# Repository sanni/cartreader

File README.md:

<br>    
<br>    
<br>   
<br>
We have moved, please visit us at https://github.com/oscartreader 🚀
<br>    
<br>    
<br>   
<br>
<br>    
<br>    
<br>   

# Open Source Cartridge Reader
This project represents a community-driven effort to provide an easy to build and easy to modify cartridge dumper.
Its main purpose is to dump a video game's ROM and save file to an SD card without the need of a PC.

For any questions you can use the [Discussions](https://github.com/sanni/cartreader/discussions) and/or [Issues](https://github.com/sanni/cartreader/issues) section here on GitHub, visit the accompanying thread in the [Arduino Forum](http://forum.arduino.cc/index.php?topic=158974.9001) or check out our [community discord server](https://discord.gg/YVxv7BnzXt), where you can reach most of the devs directly.

Also be sure to check the guides in the [Wiki](https://github.com/sanni/cartreader/wiki) too.

Happy making. 🔧🔨😊

#### Features:
- Modular design
- Stand-alone operation
- Easy to modify open-source code
- Portable when used together with a power bank

#### Supported Systems:
- NES/Famicom/Family Basic
- Super Nintendo/Super Famicom (including SF Memory, Satellaview, Sufami Turbo, and Game Processor RAM Cassettes)
- Nintendo 64 (including Controller Pak, Gameshark, and Xplorer 64)
- Game Boy Color (including GB Memory, Codebreaker, and Gameshark)
- Game Boy Advance
- Sega Mega Drive/Genesis
- Sega Master System

#### Supported with adapters:
- Virtual Boy
- Pokémon Mini
- Sega Game Gear
- Sega Mark III
- Sega SG-1000/SC-3000
- Sega Cards
- PC Engine/TurboGrafx-16/SuperGrafx
- WonderSwan (Color)
- NeoGeo Pocket (Color)
- Intellivision
- ColecoVision
- Benesse Pocket Challenge W
- Benesse Pocket Challenge V2
- Watara Supervision
- Atari 8-bit Computer (400/800/XL/XE)
- Atari 2600/5200/7800
- Atari Lynx
- Atari Jaguar
- Emerson Arcadia 2001
- Fairchild Channel F
- Magnavox Odyssey 2/Philips Videopac+
- Super A'Can
- MSX
- Casio PV-1000
- Casio Loopy
- Commodore VIC-20
- Commodore 64
- Vectrex
- Bally Astrocade
- Bandai Little Jammer
- Bandai Little Jammer Pro
- LeapFrog Leapster (L-MAX/Leapster2)
- RCA Studio II
- Texas Instruments TI-99
- Tomy Pyuuta
- TRS-80 Color Computer
- Vtech V.Smile (Baby/V.Motion)
- CPS3

#### Open Source Licenses:
- Software(everything in Cart_Reader folder) = GPL v3
- Hardware(everything in hardware folder) = CC BY 4.0
- Documentation(everything in the Wiki) = CC0 1.0

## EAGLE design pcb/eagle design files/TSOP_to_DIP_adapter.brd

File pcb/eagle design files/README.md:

With these Eagle files you can easily make your own PCB variants.    
For best compatibility be sure to use the win32 version of Eagle 7.6.0 downloaded from [here](http://eagle.autodesk.com/eagle/software-versions/2).    
All PCBs were autorouted with FreeRouting for which you need the [Java 8 RE](https://www.java.com/de/download/manual.jsp).    

#### Quick tutorial on modifying an adapter PCB:     
- Install Eagle 7.6.0 Win32    
- Copy the cam, dru, lbr and ulp folders to the Eagle main dir.    
- Open the XXX_adapter.brd file that you want to modify in Eagle PCBs.    
- In the textfield type ripup; and execute by pressing Enter key twice.    
- Go to Schematic and Board view and do your changes, watch basic Eagle tutorials to learn how.    
- Once everything is done. Go back to Board view, then File ->  Run ULP -> eagle2freerouterV6-6.ulp -> Create DSN file.     
- In Windows Explorer execute FreeRouting1.jar in ulp dir and open the XXX_adapter.dsn file you created in the previous step.     
- Let it autoroute for some hours, once finished choose Export Eagle Session script.     
- Back in Eagle in the Board view go File -> Execute Script and select the XXX_adapter.scr you just exported.     
- Next go File -> Cam Processor, File -> Open -> Job and select Elecrow_Gerber_Generater_DrillAlign.cam, then Process Job to export the Gerber files.    
- Finally inspect your gerber files with [GerberLogix](https://www.easylogix.de/products_detail.php?prog_id=1) before uploading them to JLCPCB.

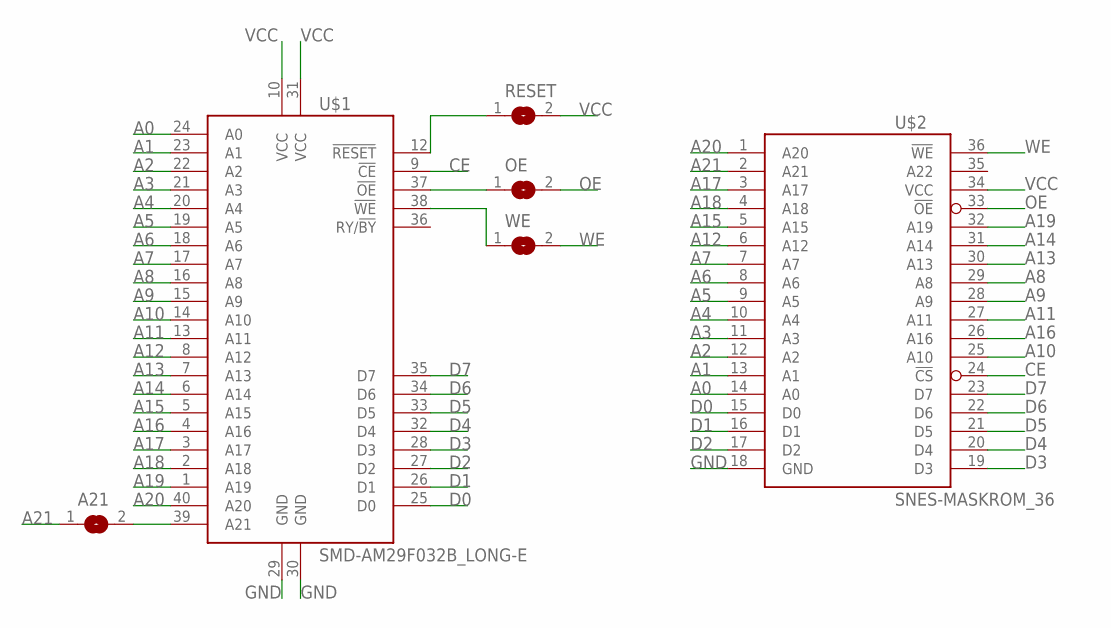
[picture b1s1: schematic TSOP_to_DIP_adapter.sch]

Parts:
A21: SMD-SOLDER_JUMPER_2; SJ
OE: SMD-SOLDER_JUMPER_2; SJ
RESET: SMD-SOLDER_JUMPER_2; SJ
U$1: SMD-AM29F032B_LONG-E; 40-TSOP_LONG
U$2: SNES-MASKROM_36; 36-PDIP
WE: SMD-SOLDER_JUMPER_2; SJ

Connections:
A0: U$1.24 (A0), U$2.14 (A0)
A1: U$1.23 (A1), U$2.13 (A1)
A2: U$1.22 (A2), U$2.12 (A2)
A3: U$1.21 (A3), U$2.11 (A3)
A4: U$1.20 (A4), U$2.10 (A4)
A5: U$1.19 (A5), U$2.9 (A5)
A6: U$1.18 (A6), U$2.8 (A6)
A7: U$1.17 (A7), U$2.7 (A7)
A8: U$1.16 (A8), U$2.29 (A8)
A9: U$1.15 (A9), U$2.28 (A9)
A10: U$1.14 (A10), U$2.25 (A10)
A11: U$1.13 (A11), U$2.27 (A11)
A12: U$1.8 (A12), U$2.6 (A12)
A13: U$1.7 (A13), U$2.30 (A13)
A14: U$1.6 (A14), U$2.31 (A14)
A15: U$1.5 (A15), U$2.5 (A15)
A16: U$1.4 (A16), U$2.26 (A16)
A17: U$1.3 (A17), U$2.3 (A17)
A18: U$1.2 (A18), U$2.4 (A18)
A19: U$1.1 (A19), U$2.32 (A19)
A20: U$1.40 (A20), U$2.1 (A20)
A21: A21.1, U$2.2 (A21)
CE: U$1.9 (!CE), U$2.24 (!CS)
D0: U$1.25 (D0), U$2.15 (D0)
D1: U$1.26 (D1), U$2.16 (D1)
D2: U$1.27 (D2), U$2.17 (D2)
D3: U$1.28 (D3), U$2.19 (D3)
D4: U$1.32 (D4), U$2.20 (D4)
D5: U$1.33 (D5), U$2.21 (D5)
D6: U$1.34 (D6), U$2.22 (D6)
D7: U$1.35 (D7), U$2.23 (D7)
GND: U$1.29 (GND), U$1.30 (GND), U$2.18 (GND)
unnamed: OE.1, U$1.37 (!OE)
unnamed: RESET.1, U$1.12 (!RESET)
unnamed: A21.2, U$1.39 (A21)
unnamed: U$1.38 (!WE), WE.1
OE: OE.2, U$2.33 (!OE)
VCC: RESET.2, U$1.10 (VCC), U$1.31 (VCC), U$2.34 (VCC)
WE: U$2.36 (!WE), WE.2

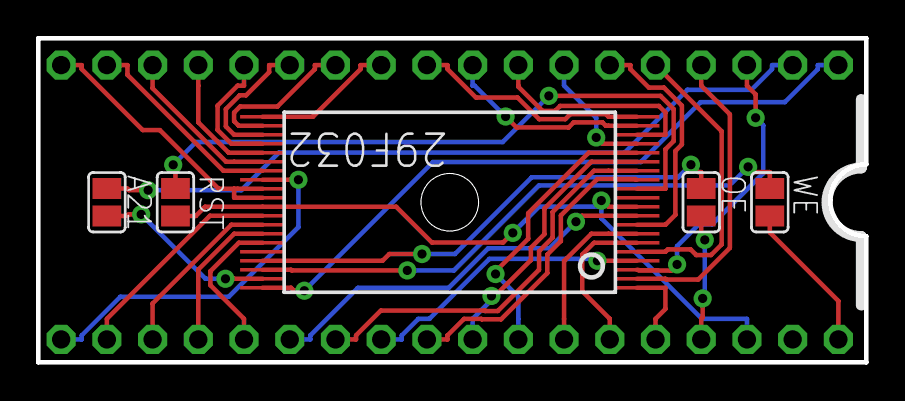
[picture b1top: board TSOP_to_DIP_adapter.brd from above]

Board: 2 copper layers, 46.0 x 18.0 mm, 6 parts (0 on the bottom side), 39 nets.

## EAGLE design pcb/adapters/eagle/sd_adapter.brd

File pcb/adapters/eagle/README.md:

With these Eagle files you can easily make your own PCB variants.    
For best compatibility be sure to use the win32 version of Eagle 7.6.0 downloaded from [here](http://eagle.autodesk.com/eagle/software-versions/2).    
All PCBs were autorouted with FreeRouting for which you need the [Java 8 RE](https://www.oracle.com/technetwork/java/javase/downloads/jre8-downloads-2133155.html).    

#### Quick tutorial on modifying an adapter PCB:     
- Install Eagle 7.6.0 Win32    
- Copy the cam, dru, lbr and ulp folders to the Eagle main dir.    
- Open the XXX_adapter.brd file that you want to modify in Eagle PCBs.    
- In the textfield type ripup; and execute by pressing Enter key twice.    
- Go to Schematic and Board view and do your changes, watch basic Eagle tutorials to learn how.    
- Once everything is done. Go back to Board view, then File ->  Run ULP -> eagle2freerouterV6-6.ulp -> Create DSN file.     
- In Windows Explorer execute FreeRouting1.jar in ulp dir and open the XXX_adapter.dsn file you created in the previous step.     
- Let it autoroute for some hours, once finished choose Export Eagle Session script.     
- Back in Eagle in the Board view go File -> Execute Script and select the XXX_adapter.scr you just exported.     
- Next go File -> Cam Processor, File -> Open -> Job and select Elecrow_Gerber_Generater_DrillAlign.cam, then Process Job to export the Gerber files.    
- Finally inspect your gerber files with [GerberLogix](https://www.easylogix.de/products_detail.php?prog_id=1) before uploading them to JLCPCB.

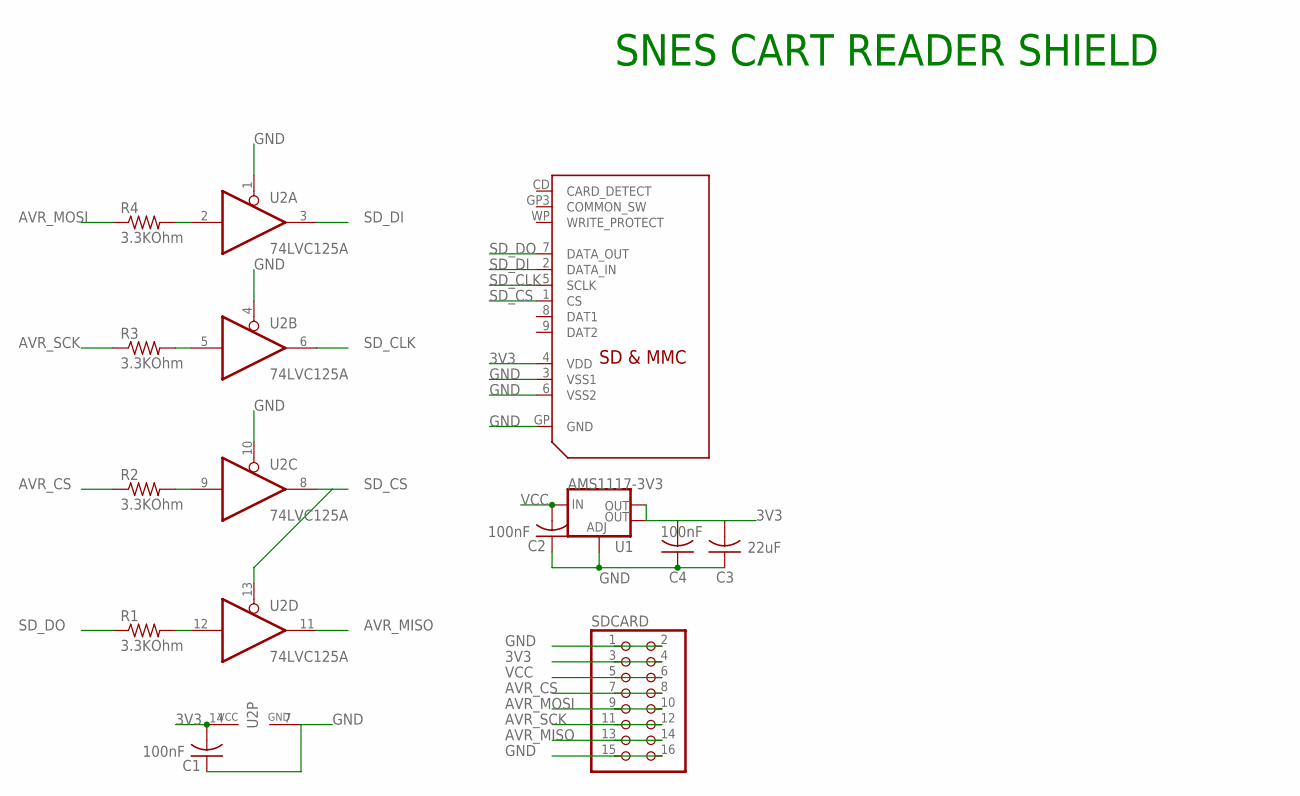
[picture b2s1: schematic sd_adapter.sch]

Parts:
C1, C2, C4: 100nF; C0805
C3: 22uF; C0805
R1, R2, R3, R4: 3.3KOhm; R0805
SDCARD: PINHD-2X8_2.54; 2X08
U1: AMS1117-3V3; SOT223
U2: 74LVC125A; TSSOP14
U$1: SDMMC06132; 06132

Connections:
3V3: C1.2, C3.2, C4.2, SDCARD.3, SDCARD.4, U1.2 (OUT), U1.4 (OUT), U2.14 (VCC), U$1.4 (VDD)
AVR_CS: R2.1, SDCARD.7, SDCARD.8
AVR_MISO: SDCARD.13, SDCARD.14, U2.11 (O)
AVR_MOSI: R4.1, SDCARD.9, SDCARD.10
AVR_SCK: R3.1, SDCARD.11, SDCARD.12
GND: C1.1, C2.1, C3.1, C4.1, SDCARD.1, SDCARD.2, SDCARD.15, SDCARD.16, U1.1 (ADJ), U2.1 (OE), U2.4 (OE), U2.7 (GND), U2.10 (OE), U$1.3 (VSS1), U$1.6 (VSS2), U$1.GP (GND)
unnamed: R1.2, U2.12 (I)
unnamed: R2.2, U2.9 (I)
unnamed: R3.2, U2.5 (I)
unnamed: R4.2, U2.2 (I)
SD_CLK: U2.6 (O), U$1.5 (SCLK)
SD_CS: U2.8 (O), U2.13 (OE), U$1.1 (CS)
SD_DI: U2.3 (O), U$1.2 (DATA_IN)
SD_DO: R1.1, U$1.7 (DATA_OUT)
VCC: C2.2, SDCARD.5, SDCARD.6, U1.3 (IN)

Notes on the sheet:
SNES CART READER SHIELD

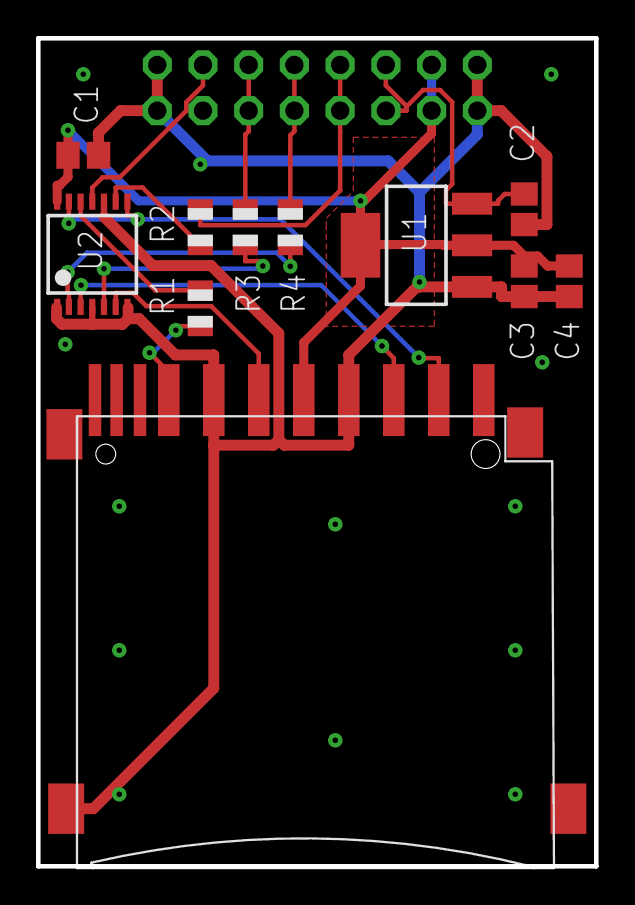
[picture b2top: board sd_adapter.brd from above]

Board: 2 copper layers, 31.0 x 46.0 mm, 12 parts (0 on the bottom side), 15 nets.

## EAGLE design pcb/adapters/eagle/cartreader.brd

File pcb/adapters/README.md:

To order adapter PCBs go to https://jlcpcb.com/ and click the "Quote now" button then upload the *_adapter.zip file of the adapter you want by clicking the "Add your Gerber file" button. It will take a while. Then in the settings below you will find "PCB Thickness" which is set to 1.6, you need to set it to 1.2 for most of the adapters or the adapter will not fit inside the SNES/N64 cart slot.    
The other settings are fine by default. Next, click the "Save to cart" button and if you want to order another adapter type click on "Add new item" button and upload the next zip file, set the thickness to 1.2mm again if needed, add to cart, and so on.     
You should get a free shipping coupon if this is your first order and you sign up on this page: https://jlcpcb.com/cheapest-PCB-way      

You can also order from [Oshpark](https://oshpark.com/) but you need to [rename *_adapter.GML to *_adapter.GKO](https://www.dropbox.com/s/0rcvhalgeu11sf8/rename.jpg?dl=0) inside the *_adapter.zip or the Oshpark website will display an error. Oshpark is great for ordering the smaller PCBs but very expensive for larger boards.   

#### nes_adapter.zip is an add-on for reading NES carts, [PCB thickness needs to be changed to 1.2mm](https://dl.dropboxusercontent.com/s/va1c72073cqfy90/pcb12.jpg?dl=1), this is very important or else it won't fit into the SNES slot. You can order a 2.5mm 72pin NES slot [here](https://www.aliexpress.com/item/32827561164.html).     

#### famicom_adapter.zip is an add-on for reading Famicom carts, [PCB thickness needs to be changed to 1.2mm](https://dl.dropboxusercontent.com/s/va1c72073cqfy90/pcb12.jpg?dl=1), this is very important or else it won't fit into the SNES slot. You can order a 2.54mm 60pin Famicom slot [here](https://www.aliexpress.com/item/32827561249.html).     

#### sms_adapter.zip is an add-on for reading Sega Master System carts. You can order a 2.54mm 50pin SMS slot [here](https://www.aliexpress.com/item/32818469880.html). The adapter is based on the [design by Raphnet](https://www.raphnet.net/electronique/sms_to_smd/index_en.php). For use with the Cart Reader ignore the SMD footprints on the PCB, the adapter does not need any components. I only bridged R5 to connect the reset line, although I'm not sure if this is even needed. Unlike the other adapters this one plugs into the MD slot.   

#### wonderswan_adapter.zip is an add-on for reading WonderSwan carts. [PCB thickness needs to be changed to 1.2mm](https://www.dropbox.com/s/va1c72073cqfy90/pcb12.jpg?dl=0), this is very important or else it won't fit into the SNES slot. (Optional) Install C1 and C2 with 10uF/16v 1210 package tantalum capacitor.

#### ngp_adapter.zip is an add-on for reading NeoGeo Pocket carts. [PCB thickness needs to be changed to 1.2mm](https://www.dropbox.com/s/va1c72073cqfy90/pcb12.jpg?dl=0), this is very important or else it won't fit into the SNES slot. 

#### flash_adapter.zip is an add-on for writing flashroms like the 29F032, 29L3211, 29LV160, [PCB thickness needs to be changed to 1.2mm](https://dl.dropboxusercontent.com/s/va1c72073cqfy90/pcb12.jpg?dl=1), this is very important or else it won't fit into the SNES slot.   

#### eprom_adapter.zip is an add-on for writing an 27C322 eprom, [PCB thickness needs to be changed to 1.2mm](https://www.dropbox.com/s/va1c72073cqfy90/pcb12.jpg?dl=0), this is very important or else it won't fit into the SNES slot.     

gba_adapter.zip and md_adapter.zip are only needed if you got an older Cart Reader version that only has a SNES and N64 slot and is missing the GBA and Mega Drive/Genesis slots.

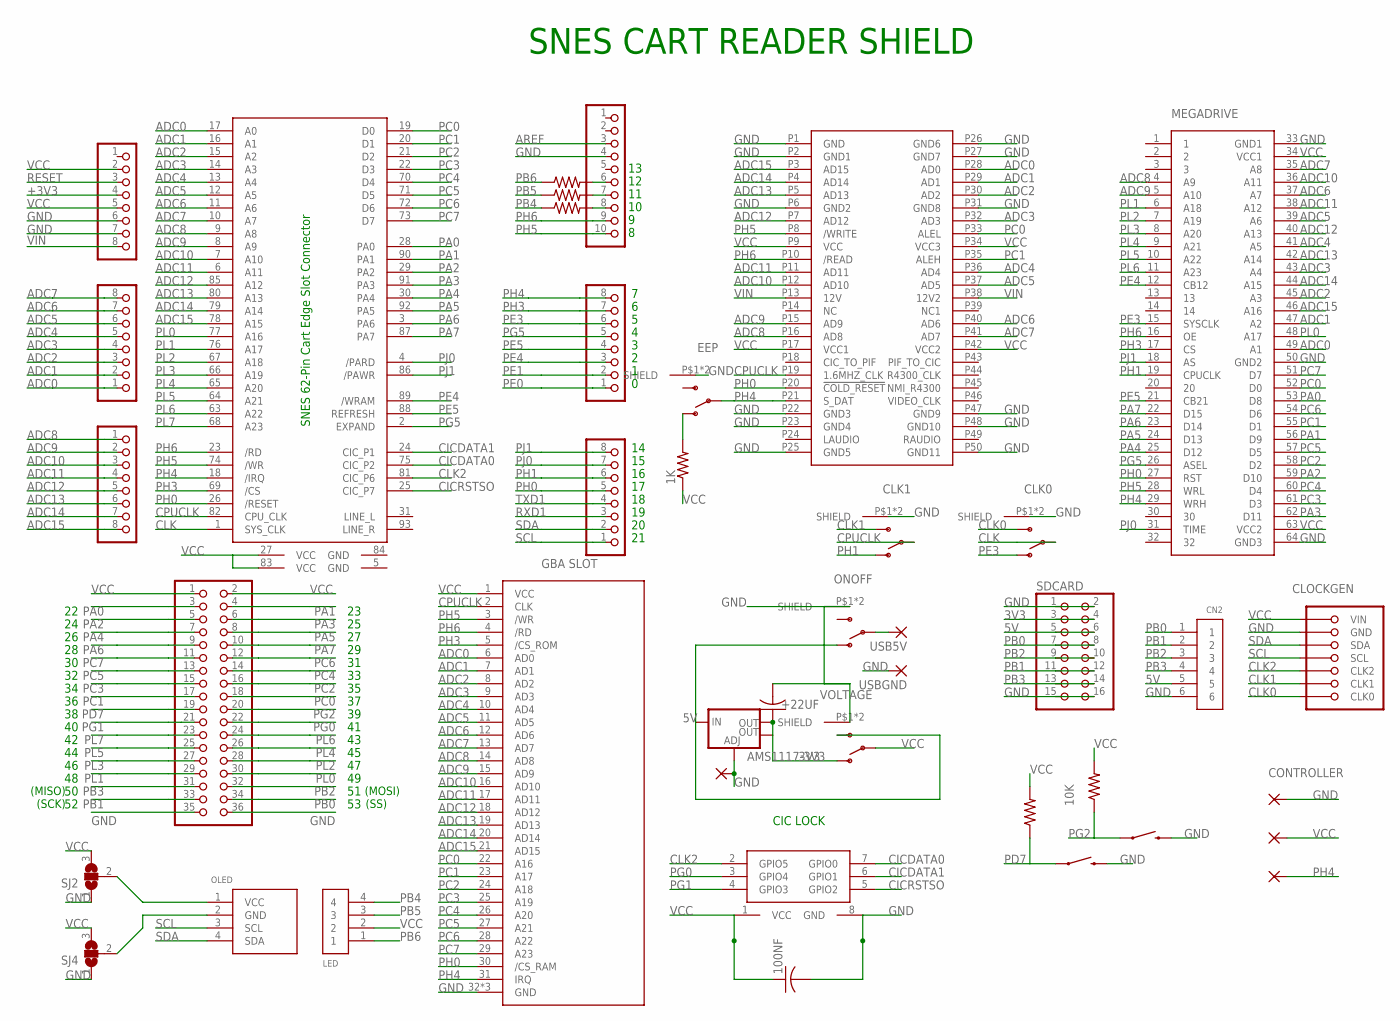
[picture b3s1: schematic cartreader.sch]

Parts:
1K, 10K, 220R, 1000R: R-US_M1206; M1206
100NF: C-USC1206; C1206
+22UF: C-USC1206; C1206
ADCH: 8x1F-H8.5; 1X08
ADCL: 8x1F-H8.5; 1X08
AMS1117-3V3: SMD-AMS1117SOT223; SOT223
CIC: PIC12F629_SIMPLE; PIC12F629
CLK0, CLK1: SWITCH-SPDT-2MMPTH; SWITCH-SPDT-2MM
CLOCKGEN: CLOCKGEN_2.54; CLOCKGEN
CN2: THT-PINHEADER_1X6-CLEANBIG; 1X06-CLEANBIG
COMMUNICATION: 8x1F-H8.5; 1X08
CONTROLLER: SMD-SOLDER_PAD; SMD1,27-2,54
EEP: SWITCH-SPDT-2MMPTH; SWITCH-SPDT-2MM
LED: THT-PINHEADER_1X4_2MM-CLEANBIG; 1X04-CLEANSMALL
MEGADRIVE: MD-CART_SLOT
OLED: OLED_I2C-CLEANBIG; OLED_I2C
ONOFF: SWITCH-SPDT-2MMPTH; SWITCH-SPDT-2MM
PAD1, PAD2, PAD3: SMD-SOLDER_PAD; SMD1,27-2,54
PINS: 10x1F-H8.5; 1X10
POWER: 8x1F-H8.5; 1X08
PWML: 8x1F-H8.5; 1X08
R19, R20: R-US_M1206; M1206
S1, S2: MOMENTARY-SWITCH-SPST-SMD-5.2MM; TACTILE_SWITCH_SMD_5.2MM
SDCARD: PINHD-2X8_2.54; 2X08
SJ2, SJ4: SJ2W; SJ_2
U$1: SNESCART_CONN_CLONE
U$2: N64-CART_SLOT_4
U$4: GBA-SLOT-BSMD; GBA-SLOT-B
USB5V: SMD-SOLDER_PAD; SMD1,27-2,54
USBGND: SMD-SOLDER_PAD; SMD1,27-2,54
VOLTAGE: SWITCH-SPDT-2MMPTH; SWITCH-SPDT-2MM
XIO: 18x2F-H8.5; 2X18

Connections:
3V3: +22UF.1, AMS1117-3V3.2 (OUT), AMS1117-3V3.4 (OUT), SDCARD.3, SDCARD.4, VOLTAGE.1 (O)
5V: AMS1117-3V3.3 (IN), CN2.5, ONOFF.1 (O), SDCARD.5, SDCARD.6, VOLTAGE.3 (S)
+3V3: POWER.4
ADC0: ADCL.1, MEGADRIVE.49 (A1), U$1.17 (A0), U$2.P28 (AD0), U$4.6 (AD0)
ADC1: ADCL.2, MEGADRIVE.47 (A2), U$1.16 (A1), U$2.P29 (AD1), U$4.7 (AD1)
ADC2: ADCL.3, MEGADRIVE.45 (A3), U$1.15 (A2), U$2.P30 (AD2), U$4.8 (AD2)
ADC3: ADCL.4, MEGADRIVE.43 (A4), U$1.14 (A3), U$2.P32 (AD3), U$4.9 (AD3)
ADC4: ADCL.5, MEGADRIVE.41 (A5), U$1.13 (A4), U$2.P36 (AD4), U$4.10 (AD4)
ADC5: ADCL.6, MEGADRIVE.39 (A6), U$1.12 (A5), U$2.P37 (AD5), U$4.11 (AD5)
ADC6: ADCL.7, MEGADRIVE.37 (A7), U$1.11 (A6), U$2.P40 (AD6), U$4.12 (AD6)
ADC7: ADCL.8, MEGADRIVE.35 (A8), U$1.10 (A7), U$2.P41 (AD7), U$4.13 (AD7)
ADC8: ADCH.1, MEGADRIVE.4 (A9), U$1.9 (A8), U$2.P16 (AD8), U$4.14 (AD8)
ADC9: ADCH.2, MEGADRIVE.5 (A10), U$1.8 (A9), U$2.P15 (AD9), U$4.15 (AD9)
ADC10: ADCH.3, MEGADRIVE.36 (A11), U$1.7 (A10), U$2.P12 (AD10), U$4.16 (AD10)
ADC11: ADCH.4, MEGADRIVE.38 (A12), U$1.6 (A11), U$2.P11 (AD11), U$4.17 (AD11)
ADC12: ADCH.5, MEGADRIVE.40 (A13), U$1.85 (A12), U$2.P7 (AD12), U$4.18 (AD12)
ADC13: ADCH.6, MEGADRIVE.42 (A14), U$1.80 (A13), U$2.P5 (AD13), U$4.19 (AD13)
ADC14: ADCH.7, MEGADRIVE.44 (A15), U$1.79 (A14), U$2.P4 (AD14), U$4.20 (AD14)
ADC15: ADCH.8, MEGADRIVE.46 (A16), U$1.78 (A15), U$2.P3 (AD15), U$4.21 (AD15)
AREF: PINS.3
CICDATA0: CIC.7 (GPIO0), U$1.75 (CIC_P2)
CICDATA1: CIC.6 (GPIO1), U$1.24 (CIC_P1)
CICRSTSO: CIC.5 (GPIO2), U$1.25 (CIC_P7)
CLK: CLK0.2, U$1.1 (SYS_CLK)
CLK0: CLK0.3 (S), CLOCKGEN.7 (CLK0)
CLK1: CLK1.3 (S), CLOCKGEN.6 (CLK1)
CLK2: CIC.2 (GPIO5), CLOCKGEN.5 (CLK2), U$1.81 (CIC_P6)
CPUCLK: CLK1.2, U$1.82 (CPU_CLK), U$2.P19 (1.6MHZ_CLK), U$4.2 (CLK)
GND: 100NF.2, +22UF.2, AMS1117-3V3.1 (ADJ), CIC.8 (GND), CLK0.P$1 (SHIELD), CLK0.P$2 (SHIELD), CLK1.P$1 (SHIELD), CLK1.P$2 (SHIELD), CLOCKGEN.2 (GND), CN2.6, EEP.P$1 (SHIELD), EEP.P$2 (SHIELD), MEGADRIVE.33 (GND1), MEGADRIVE.50 (GND2), MEGADRIVE.64 (GND3), ONOFF.P$1 (SHIELD), ONOFF.P$2 (SHIELD), PAD1.1, PAD2.1, PINS.4, POWER.6, POWER.7, S1.3 (2), S2.3 (2), SDCARD.1, SDCARD.2, SDCARD.15, SDCARD.16, SJ2.1, SJ4.1, U$1.5 (GND), U$1.84 (GND), U$2.P1 (GND), U$2.P2 (GND1), U$2.P6 (GND2), U$2.P22 (GND3), U$2.P23 (GND4), U$2.P25 (GND5), U$2.P26 (GND6), U$2.P27 (GND7), U$2.P31 (GND8), U$2.P47 (GND9), U$2.P48 (GND10), U$2.P50 (GND11), U$4.32 (GND), U$4.SHIELD_3 (GND), U$4.SHIELD_4 (GND), USBGND.1, VOLTAGE.P$1 (SHIELD), VOLTAGE.P$2 (SHIELD), XIO.35, XIO.36
unnamed: 1K.2, EEP.1 (O)
unnamed: ONOFF.2, USB5V.1
unnamed: OLED.1 (VCC), SJ2.2
unnamed: OLED.2 (GND), SJ4.2
unnamed: 220R.2, PINS.6
unnamed: PINS.7, R19.2
unnamed: PINS.8, R20.2
PA0: MEGADRIVE.53 (D8), U$1.28 (PA0), XIO.3
PA1: MEGADRIVE.56 (D9), U$1.90 (PA1), XIO.4
PA2: MEGADRIVE.59 (D10), U$1.29 (PA2), XIO.5
PA3: MEGADRIVE.62 (D11), U$1.91 (PA3), XIO.6
PA4: MEGADRIVE.25 (D12), U$1.30 (PA4), XIO.7
PA5: MEGADRIVE.24 (D13), U$1.92 (PA5), XIO.8
PA6: MEGADRIVE.23 (D14), U$1.3 (PA6), XIO.9
PA7: MEGADRIVE.22 (D15), U$1.87 (PA7), XIO.10
PB0: CN2.1, SDCARD.7, SDCARD.8, XIO.34
PB1: CN2.2, SDCARD.11, SDCARD.12, XIO.33
PB2: CN2.3, SDCARD.9, SDCARD.10, XIO.32
PB3: CN2.4, SDCARD.13, SDCARD.14, XIO.31
PB4: LED.4, R20.1
PB5: LED.3, R19.1
PB6: 220R.1, LED.1
PC0: MEGADRIVE.52 (D0), U$1.19 (D0), U$2.P33 (ALEL), U$4.22 (A16), XIO.18
PC1: MEGADRIVE.55 (D1), U$1.20 (D1), U$2.P35 (ALEH), U$4.23 (A17), XIO.17
PC2: MEGADRIVE.58 (D2), U$1.21 (D2), U$4.24 (A18), XIO.16
PC3: MEGADRIVE.61 (D3), U$1.22 (D3), U$4.25 (A19), XIO.15
PC4: MEGADRIVE.60 (D4), U$1.70 (D4), U$4.26 (A20), XIO.14
PC5: MEGADRIVE.57 (D5), U$1.71 (D5), U$4.27 (A21), XIO.13
PC6: MEGADRIVE.54 (D6), U$1.72 (D6), U$4.28 (A22), XIO.12
PC7: MEGADRIVE.51 (D7), U$1.73 (D7), U$4.29 (A23), XIO.11
PD7: 10K.1, S1.1, XIO.19
PE0: PWML.1
PE1: PWML.2
PE3: CLK0.1 (O), MEGADRIVE.15 (SYSCLK), PWML.6
PE4: MEGADRIVE.12 (CB12), PWML.3, U$1.89 (/WRAM)
PE5: MEGADRIVE.21 (CB21), PWML.4, U$1.88 (REFRESH)
PG0: CIC.3 (GPIO4), XIO.22
PG1: CIC.4 (GPIO3), XIO.21
PG2: 1000R.1, S2.1, XIO.20
PG5: MEGADRIVE.26 (ASEL), PWML.5, U$1.2 (EXPAND)
PH0: COMMUNICATION.5, MEGADRIVE.27 (RST), U$1.26 (/RESET), U$2.P20 (!COLD_RESET), U$4.30 (/CS_RAM)
PH1: CLK1.1 (O), COMMUNICATION.6, MEGADRIVE.19 (CPUCLK)
PH3: MEGADRIVE.17 (CS), PWML.7, U$1.69 (/CS), U$4.5 (/CS_ROM)
PH4: CONTROLLER.1, EEP.2, MEGADRIVE.29 (WRH), PWML.8, U$1.18 (/IRQ), U$2.P21 (S_DAT), U$4.31 (IRQ)
PH5: MEGADRIVE.28 (WRL), PINS.10, U$1.74 (/WR), U$2.P8 (/WRITE), U$4.3 (/WR)
PH6: MEGADRIVE.16 (OE), PINS.9, U$1.23 (/RD), U$2.P10 (/READ), U$4.4 (/RD)
PJ0: COMMUNICATION.7, MEGADRIVE.31 (TIME), U$1.4 (/PARD)
PJ1: COMMUNICATION.8, MEGADRIVE.18 (AS), U$1.86 (/PAWR)
PL0: MEGADRIVE.48 (A17), U$1.77 (A16), XIO.30
PL1: MEGADRIVE.6 (A18), U$1.76 (A17), XIO.29
PL2: MEGADRIVE.7 (A19), U$1.67 (A18), XIO.28
PL3: MEGADRIVE.8 (A20), U$1.66 (A19), XIO.27
PL4: MEGADRIVE.9 (A21), U$1.65 (A20), XIO.26
PL5: MEGADRIVE.10 (A22), U$1.64 (A21), XIO.25
PL6: MEGADRIVE.11 (A23), U$1.63 (A22), XIO.24
PL7: U$1.68 (A23), XIO.23
RESET: POWER.3
RXD1: COMMUNICATION.3
SCL: CLOCKGEN.4 (SCL), COMMUNICATION.1, OLED.3 (SCL)
SDA: CLOCKGEN.3 (SDA), COMMUNICATION.2, OLED.4 (SDA)
TXD1: COMMUNICATION.4
VCC: 1K.1, 10K.2, 100NF.1, 1000R.2, CIC.1 (VCC), CLOCKGEN.1 (VIN), LED.2, MEGADRIVE.34 (VCC1), MEGADRIVE.63 (VCC2), PAD3.1, POWER.2, POWER.5, SJ2.3, SJ4.3, U$1.27 (VCC), U$1.83 (VCC), U$2.P9 (VCC), U$2.P17 (VCC1), U$2.P34 (VCC3), U$2.P42 (VCC2), U$4.1 (VCC), VOLTAGE.2, XIO.1, XIO.2
VIN: POWER.8, U$2.P13 (12V), U$2.P38 (12V2)

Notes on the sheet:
(SS)
(MOSI)
(SCK)
(MISO)
SNES CART READER SHIELD
CIC LOCK
SNES 62-Pin Cart Edge Slot Connector

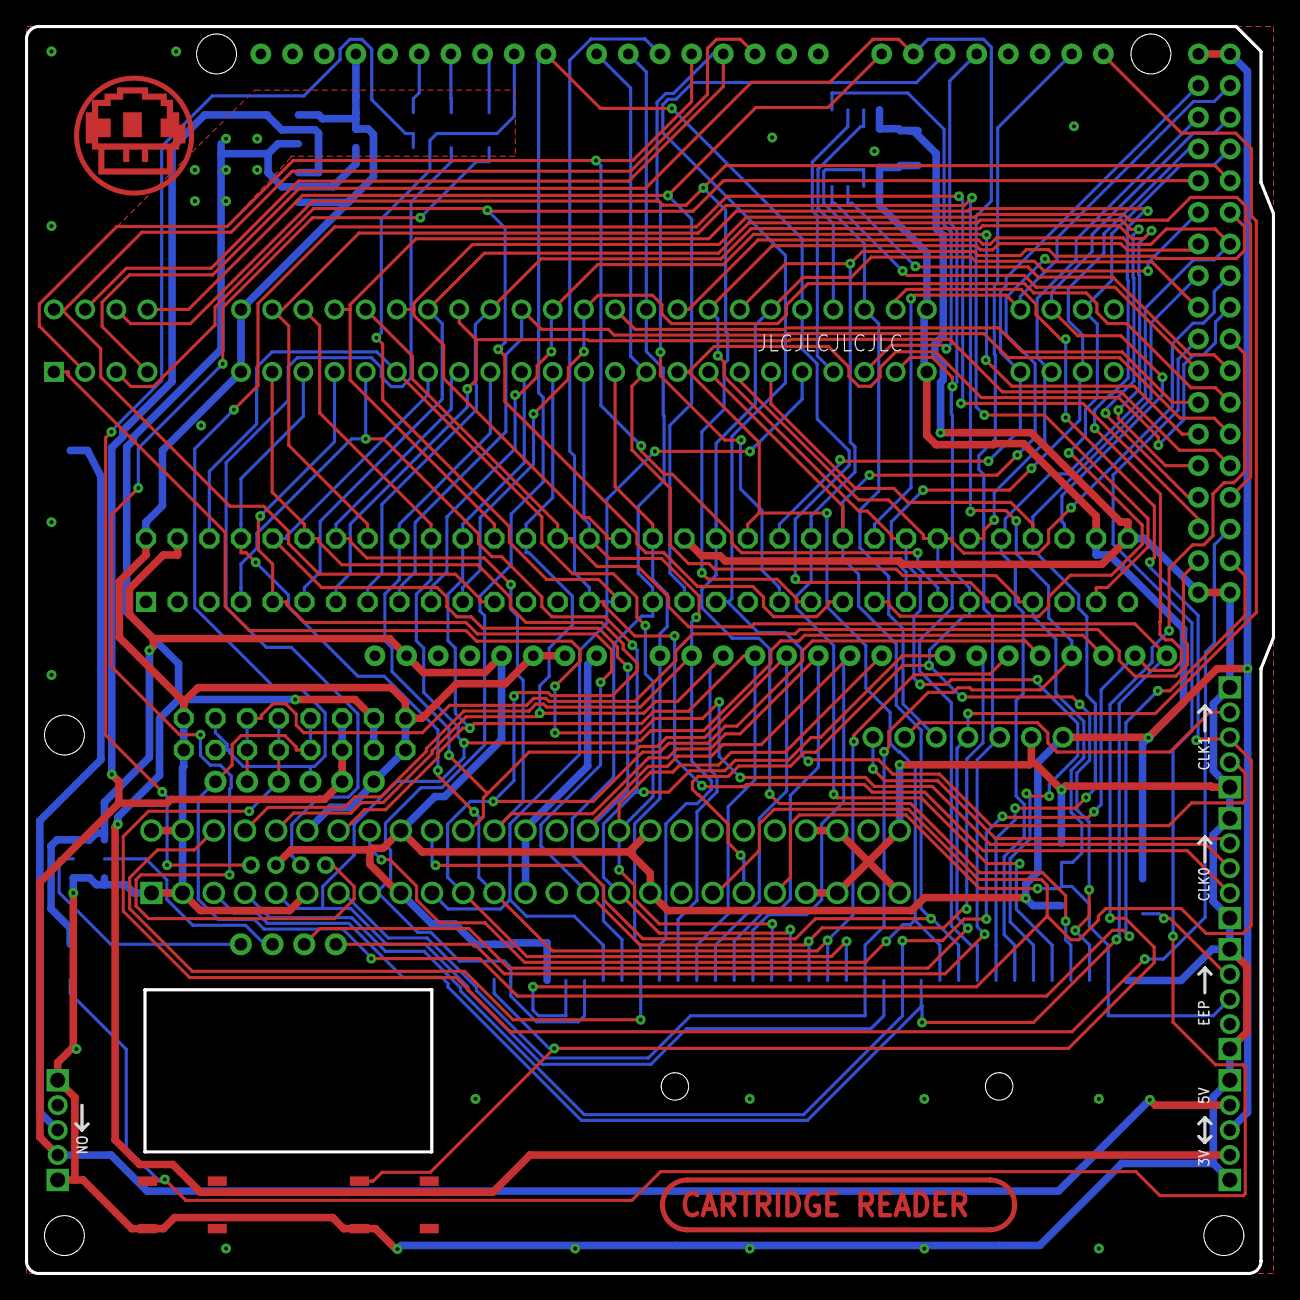
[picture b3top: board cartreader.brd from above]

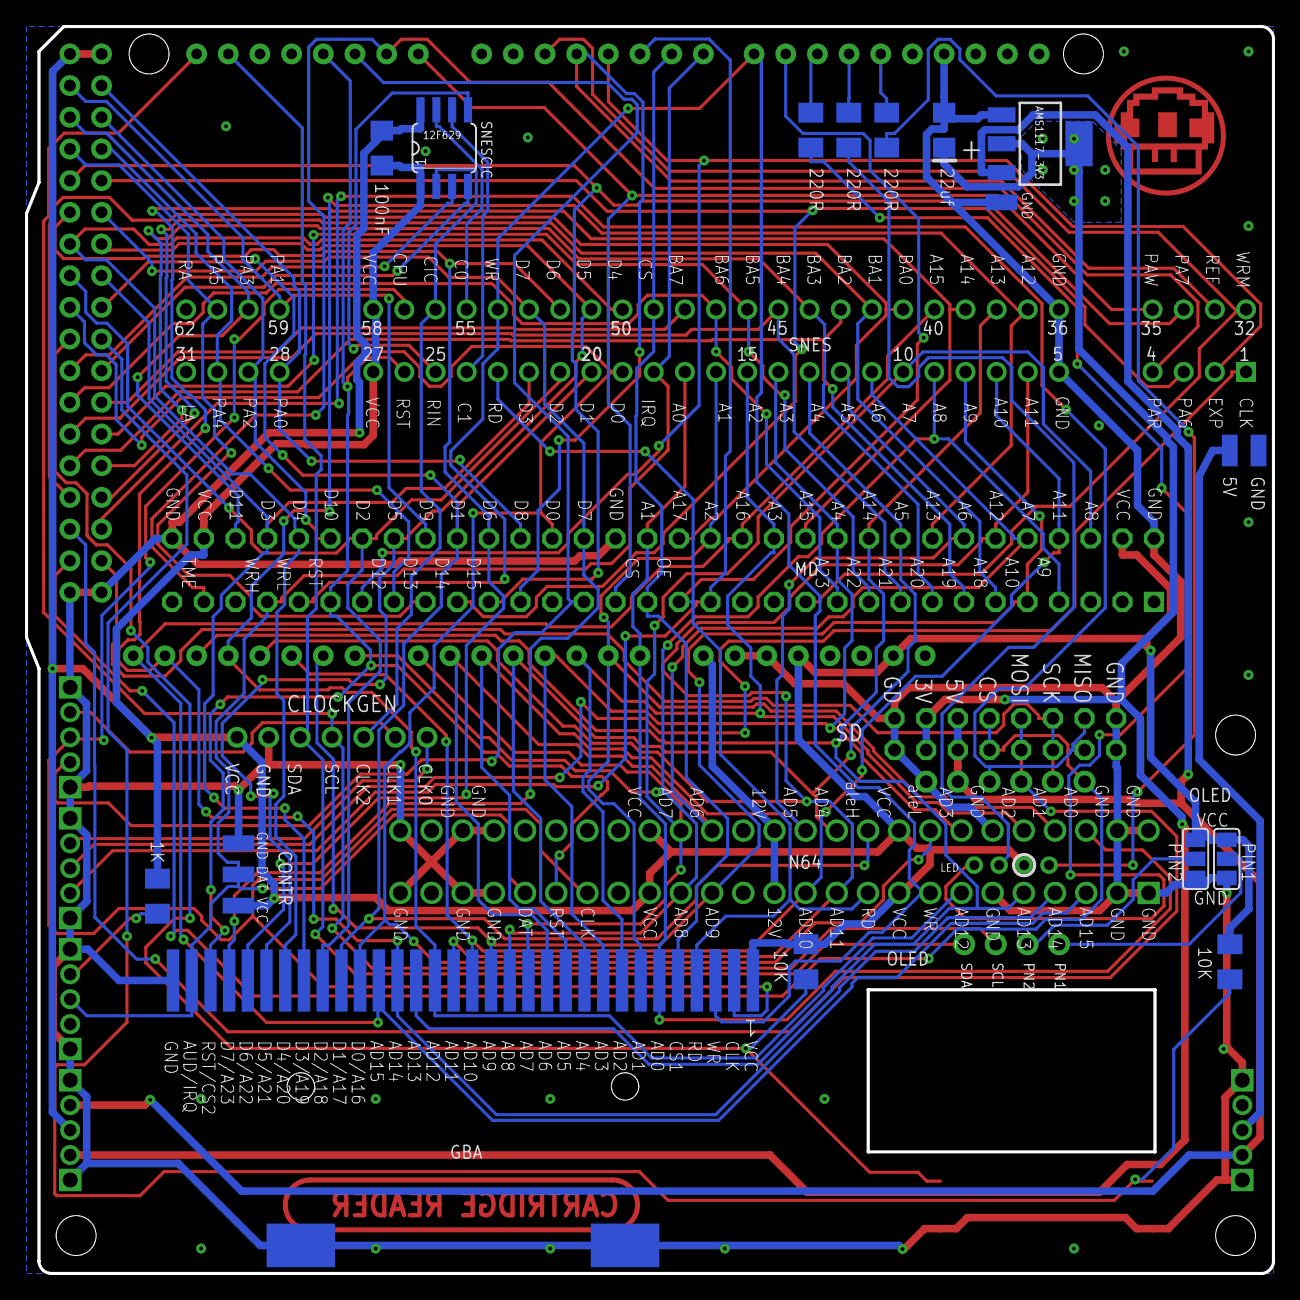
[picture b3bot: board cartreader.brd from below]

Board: 2 copper layers, 100.0 x 100.0 mm, 41 parts (24 on the bottom side), 85 nets.

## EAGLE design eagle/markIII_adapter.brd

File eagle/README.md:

With these files you can easily make your own adapters.    
For best compatibility be sure to use the win32 version of Eagle 7.6.0 downloaded from [here](http://eagle.autodesk.com/eagle/software-versions/2).    
All PCBs were autorouted with FreeRouting for which you need the [Java 8 RE](https://www.oracle.com/technetwork/java/javase/downloads/jre8-downloads-2133155.html).    

#### Quick tutorial on modifying an adapter PCB:     
- Install Eagle 7.6.0 Win32    
- Copy the cam, dru, lbr and ulp folders to the Eagle main dir.    
- Open the XXX_adapter.brd file that you want to modify in Eagle PCBs.    
- In the textfield type ripup; and execute by pressing Enter key twice.    
- Go to Schematic and Board view and do your changes, watch basic Eagle tutorials to learn how.    
- Once everything is done. Go back to Board view, then File ->  Run ULP -> eagle2freerouterV6-6.ulp -> Create DSN file.     
- In Windows Explorer execute FreeRouting1.jar in ulp dir and open the XXX_adapter.dsn file you created in the previous step.     
- Let it autoroute for some hours, once finished choose Export Eagle Session script.     
- Back in Eagle in the Board view go File -> Execute Script and select the XXX_adapter.scr you just exported.     
- Finally go File -> Cam Processor, File -> Open -> Job and select Elecrow_Gerber_Generater_DrillAlign.cam, then Process Job to export the Gerber files.

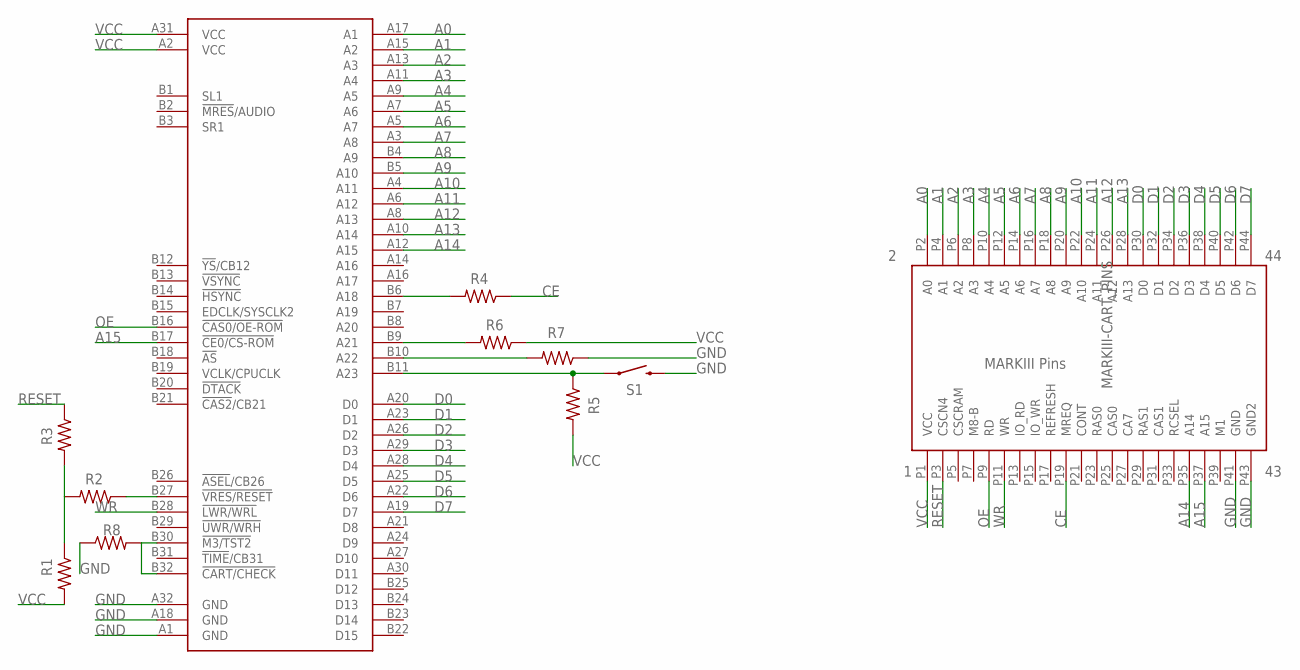
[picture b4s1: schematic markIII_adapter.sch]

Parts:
CN3: MEGADRIVE-CART-CONNECTOR-ORDERED; MEGADRIVE-CART-CONNECTOR
R1, R4, R6, R7, R8: 0; M1206
R2, R3: NP; M1206
R5: 56K; M1206
S1: MOMENTARY-SWITCH-SPST-SMD-5.2MM; TACTILE_SWITCH_SMD_5.2MM
U$1: MARKIII-CART_PINS; MARKIII_PINS

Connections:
A0: CN3.A17 (A1), U$1.P2 (A0)
A1: CN3.A15 (A2), U$1.P4 (A1)
A2: CN3.A13 (A3), U$1.P6 (A2)
A3: CN3.A11 (A4), U$1.P8 (A3)
A4: CN3.A9 (A5), U$1.P10 (A4)
A5: CN3.A7 (A6), U$1.P12 (A5)
A6: CN3.A5 (A7), U$1.P14 (A6)
A7: CN3.A3 (A8), U$1.P16 (A7)
A8: CN3.B4 (A9), U$1.P18 (A8)
A9: CN3.B5 (A10), U$1.P20 (A9)
A10: CN3.A4 (A11), U$1.P22 (A10)
A11: CN3.A6 (A12), U$1.P24 (A11)
A12: CN3.A8 (A13), U$1.P26 (A12)
A13: CN3.A10 (A14), U$1.P28 (A13)
A14: CN3.A12 (A15), U$1.P35 (A14)
A15: CN3.B17 (!CE0/CS-ROM), U$1.P37 (A15)
CE: R4.1, U$1.P19 (MREQ)
D0: CN3.A20 (D0), U$1.P30 (D0)
D1: CN3.A23 (D1), U$1.P32 (D1)
D2: CN3.A26 (D2), U$1.P34 (D2)
D3: CN3.A29 (D3), U$1.P36 (D3)
D4: CN3.A28 (D4), U$1.P38 (D4)
D5: CN3.A25 (D5), U$1.P40 (D5)
D6: CN3.A22 (D6), U$1.P42 (D6)
D7: CN3.A19 (D7), U$1.P44 (D7)
GND: CN3.A1 (GND), CN3.A18 (GND), CN3.A32 (GND), R7.1, R8.1, S1.3 (2), U$1.P41 (GND), U$1.P43 (GND2)
unnamed: CN3.B11 (A23), R5.1, S1.1
unnamed: CN3.B10 (A22), R7.2
unnamed: CN3.B9 (A21), R6.2
unnamed: R1.1, R2.2, R3.2
unnamed: CN3.B30 (!M3/TST2), CN3.B32 (!CART/CHECK), R8.2
unnamed: CN3.B27 (!VRES/RESET), R2.1
unnamed: CN3.B6 (A18), R4.2
OE: CN3.B16 (!CAS0/OE-ROM), U$1.P9 (RD)
RESET: R3.1, U$1.P3 (CSCN4)
VCC: CN3.A2 (VCC), CN3.A31 (VCC), R1.2, R5.2, R6.1, U$1.P1 (VCC)
WR: CN3.B28 (!LWR/WRL), U$1.P11 (WR)

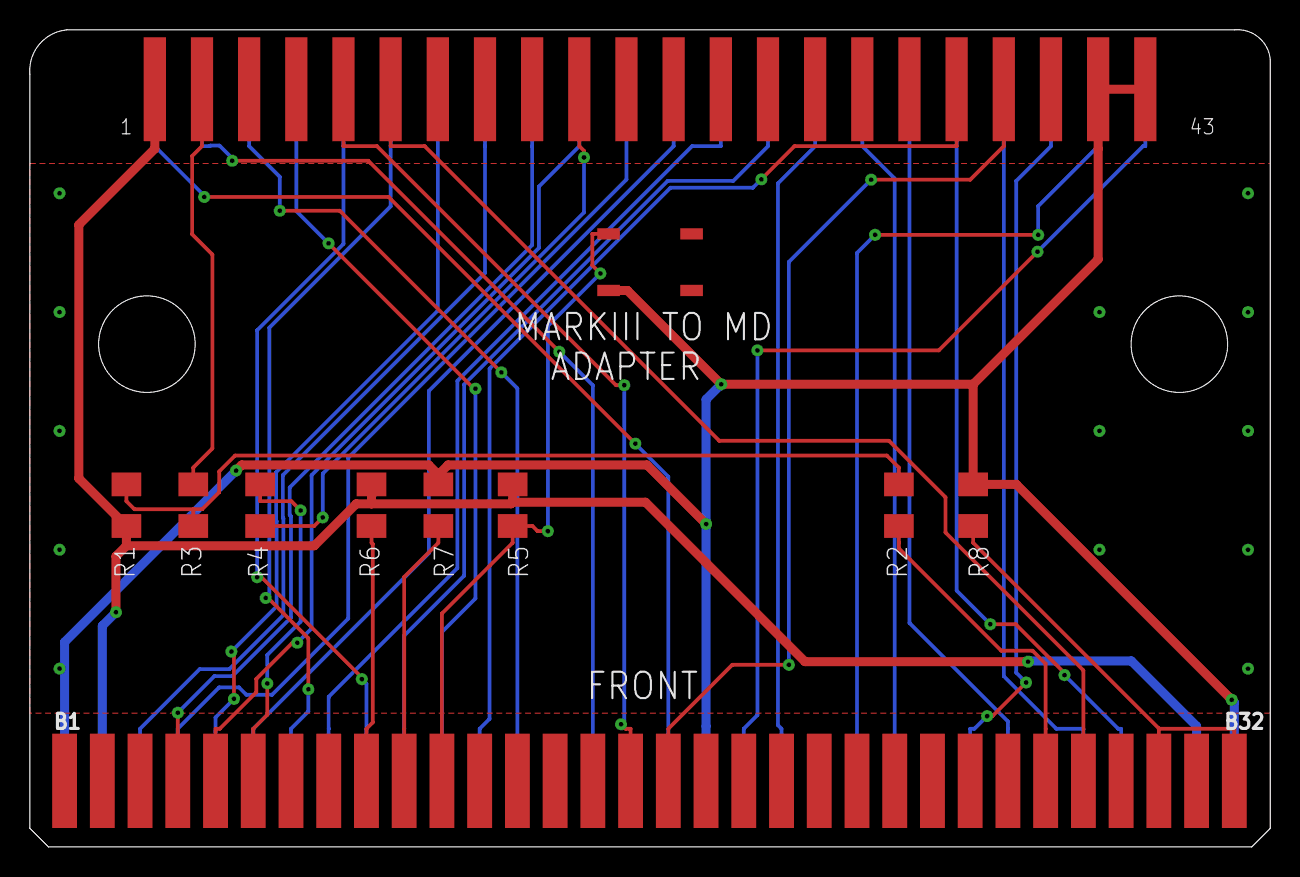
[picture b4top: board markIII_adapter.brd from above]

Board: 2 copper layers, 83.5 x 55.0 mm, 11 parts (0 on the bottom side), 37 nets.

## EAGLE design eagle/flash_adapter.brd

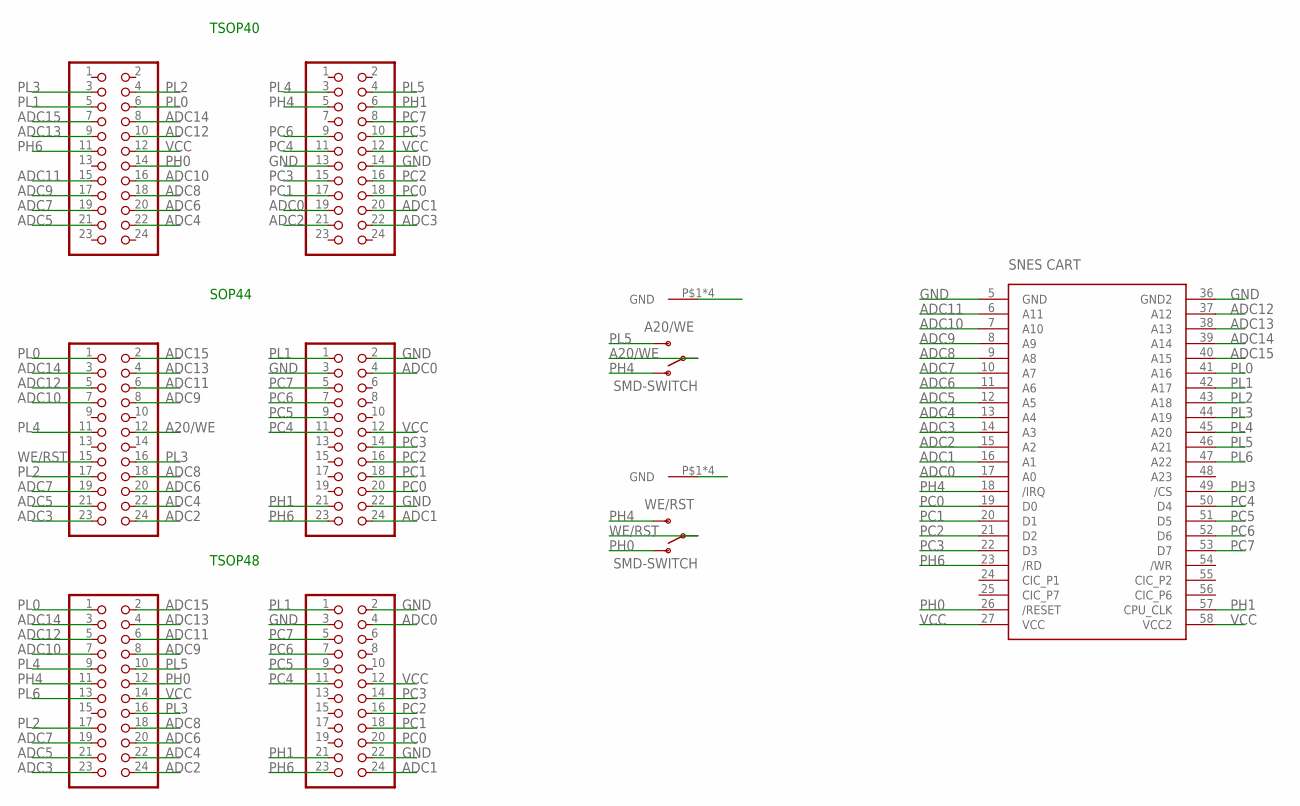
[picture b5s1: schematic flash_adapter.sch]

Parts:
A20/WE: SMD-SWITCH
JP1, JP2, JP3, JP4, JP5, JP6: PINHD-2X12; 2X12
U$1: SNES-CART_PINS_LONG; SNESCART_PINS_LONG
WE/RST: SMD-SWITCH

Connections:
A20/WE: A20/WE.P, JP1.12
ADC0: JP2.4, JP4.4, JP6.19, U$1.17 (A0)
ADC1: JP2.24, JP4.24, JP6.20, U$1.16 (A1)
ADC2: JP1.24, JP3.24, JP6.21, U$1.15 (A2)
ADC3: JP1.23, JP3.23, JP6.22, U$1.14 (A3)
ADC4: JP1.22, JP3.22, JP5.22, U$1.13 (A4)
ADC5: JP1.21, JP3.21, JP5.21, U$1.12 (A5)
ADC6: JP1.20, JP3.20, JP5.20, U$1.11 (A6)
ADC7: JP1.19, JP3.19, JP5.19, U$1.10 (A7)
ADC8: JP1.18, JP3.18, JP5.18, U$1.9 (A8)
ADC9: JP1.8, JP3.8, JP5.17, U$1.8 (A9)
ADC10: JP1.7, JP3.7, JP5.16, U$1.7 (A10)
ADC11: JP1.6, JP3.6, JP5.15, U$1.6 (A11)
ADC12: JP1.5, JP3.5, JP5.10, U$1.37 (A12)
ADC13: JP1.4, JP3.4, JP5.9, U$1.38 (A13)
ADC14: JP1.3, JP3.3, JP5.8, U$1.39 (A14)
ADC15: JP1.2, JP3.2, JP5.7, U$1.40 (A15)
GND: A20/WE.P$1 (GND), A20/WE.P$2 (GND), A20/WE.P$3 (GND), A20/WE.P$4 (GND), JP2.2, JP2.3, JP2.22, JP4.2, JP4.3, JP4.22, JP6.13, JP6.14, U$1.5 (GND), U$1.36 (GND2), WE/RST.P$1 (GND), WE/RST.P$2 (GND), WE/RST.P$3 (GND), WE/RST.P$4 (GND)
PC0: JP2.20, JP4.20, JP6.18, U$1.19 (D0)
PC1: JP2.18, JP4.18, JP6.17, U$1.20 (D1)
PC2: JP2.16, JP4.16, JP6.16, U$1.21 (D2)
PC3: JP2.14, JP4.14, JP6.15, U$1.22 (D3)
PC4: JP2.11, JP4.11, JP6.11, U$1.50 (D4)
PC5: JP2.9, JP4.9, JP6.10, U$1.51 (D5)
PC6: JP2.7, JP4.7, JP6.9, U$1.52 (D6)
PC7: JP2.5, JP4.5, JP6.8, U$1.53 (D7)
PH0: JP3.12, JP5.14, U$1.26 (/RESET), WE/RST.O
PH1: JP2.21, JP4.21, JP6.6, U$1.57 (CPU_CLK)
PH3: U$1.49 (/CS)
PH4: A20/WE.O, JP3.11, JP6.5, U$1.18 (/IRQ), WE/RST.S
PH6: JP2.23, JP4.23, JP5.11, U$1.23 (/RD)
PL0: JP1.1, JP3.1, JP5.6, U$1.41 (A16)
PL1: JP2.1, JP4.1, JP5.5, U$1.42 (A17)
PL2: JP1.17, JP3.17, JP5.4, U$1.43 (A18)
PL3: JP1.16, JP3.16, JP5.3, U$1.44 (A19)
PL4: JP1.11, JP3.9, JP6.3, U$1.45 (A20)
PL5: A20/WE.S, JP3.10, JP6.4, U$1.46 (A21)
PL6: JP3.13, U$1.47 (A22)
VCC: JP2.12, JP3.14, JP4.12, JP5.12, JP6.12, U$1.27 (VCC), U$1.58 (VCC2)
WE/RST: JP1.15, WE/RST.P

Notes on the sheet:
SOP44
TSOP48
TSOP40

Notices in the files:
Cart_Reader/SMS.ino:
Fix for "Fantasy Zone (J) (V1.0)" that has not the normal header, but "COPYRIGHT SEGAPRG. BY T.ASAI".
if (strcmp(headerFZ, "COPYRIGHT SEGAPRG. BY T.ASAI") == 0) {
parts and their libraries:
SparkFun-Aesthetics: Licensing: Creative Commons ShareAlike 4.0 International - https://creativecommons.org/licenses/by-sa/4.0
